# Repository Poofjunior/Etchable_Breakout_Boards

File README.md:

# A Collection of Etchable Breakout Boards

## Basic Info  
To open these breakout boards, you'll need the 
[HMCEagleLibrary](https://github.com/Poofjunior/HMCEagleLibrary)

Be careful when etching!

## References

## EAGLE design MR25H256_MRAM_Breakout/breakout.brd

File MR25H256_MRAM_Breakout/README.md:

# MR25H256 Etchable Breakout Board

## Basic Info  
The MR25H256 is a 262 kilobit magnetoresistive random-access memory chip 
that communicates over SPI interface. 

Be careful when etching!

## References
1. [The Datasheet](http://media.digikey.com/pdf/Data%20Sheets/EverSpin%20Technologies/MR25H256_Datasheet_Rev8.pdf)

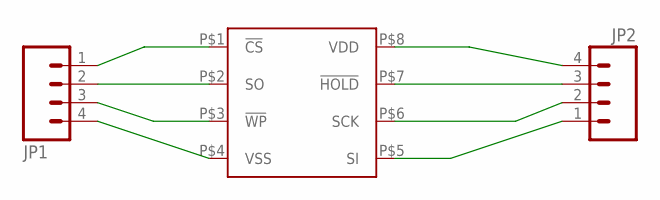
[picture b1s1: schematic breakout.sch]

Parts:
JP1, JP2: M04PTH; 1X04
U$1: MR25H256; DFN8

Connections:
unnamed: JP1.1, U$1.P$1 (!CS)
unnamed: JP1.2, U$1.P$2 (SO)
unnamed: JP1.3, U$1.P$3 (!WP)
unnamed: JP1.4, U$1.P$4 (VSS)
unnamed: JP2.1, U$1.P$5 (SI)
unnamed: JP2.2, U$1.P$6 (SCK)
unnamed: JP2.3, U$1.P$7 (!HOLD)
unnamed: JP2.4, U$1.P$8 (VDD)

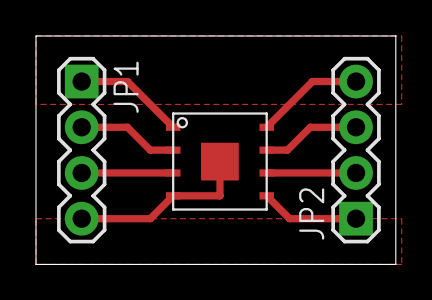
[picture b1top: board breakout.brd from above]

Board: 2 copper layers, 20.0 x 12.7 mm, 3 parts (0 on the bottom side), 8 nets.

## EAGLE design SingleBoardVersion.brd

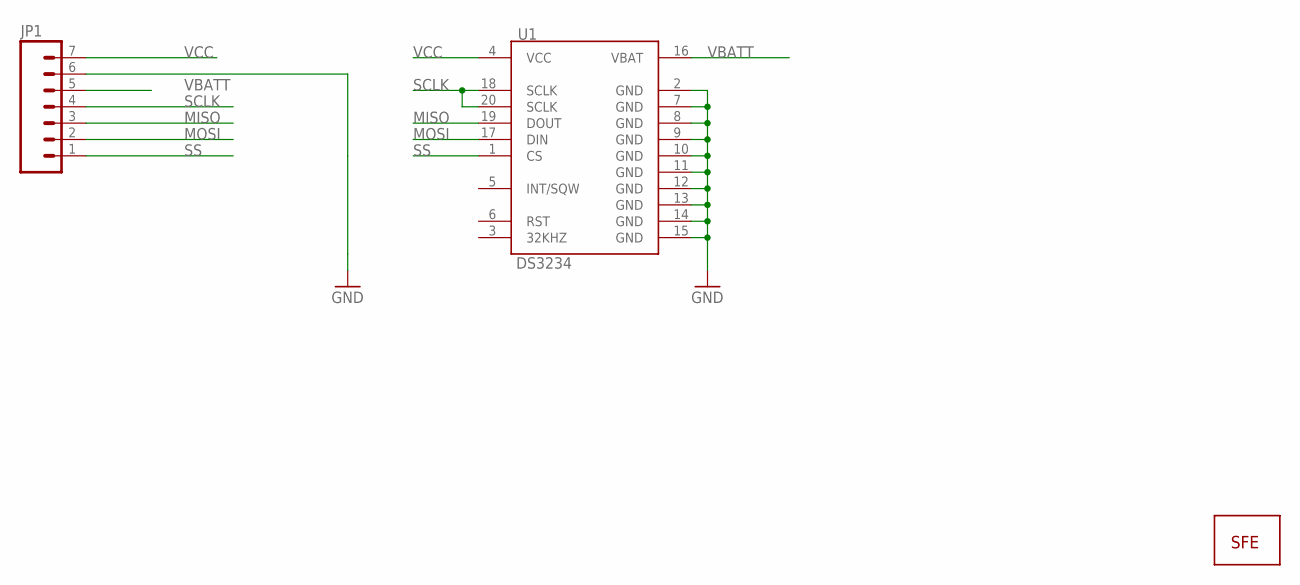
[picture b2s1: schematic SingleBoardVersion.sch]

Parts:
JP1: M07; 1X07
JP2: LOGO-SFESK; SFE-LOGO-FLAME
U1: DS3234

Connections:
GND: JP1.6, U1.2 (GND), U1.7 (GND), U1.8 (GND), U1.9 (GND), U1.10 (GND), U1.11 (GND), U1.12 (GND), U1.13 (GND), U1.14 (GND), U1.15 (GND)
MISO: JP1.3, U1.19 (DOUT)
MOSI: JP1.2, U1.17 (DIN)
SCLK: JP1.4, U1.18 (SCLK), U1.20 (SCLK)
SS: JP1.1, U1.1 (CS)
VBATT: JP1.5, U1.16 (VBAT)
VCC: JP1.7, U1.4 (VCC)

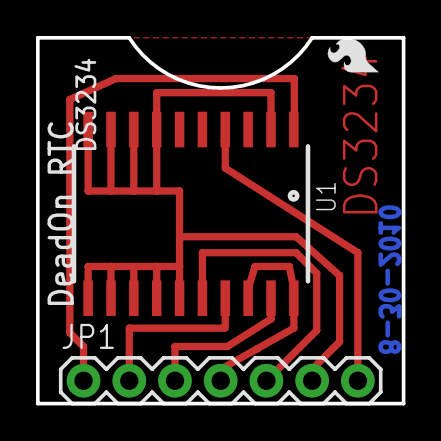
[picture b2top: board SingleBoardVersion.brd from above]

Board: 2 copper layers, 20.3 x 20.3 mm, 4 parts (0 on the bottom side), 7 nets.

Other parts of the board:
U2: CREATIVE_COMMONS

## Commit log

2013-02-22 added .gitignore
2013-02-24 updated README with references
2013-02-24 updated README with correct links
2013-02-24 added a picture
2013-02-24 fixed image size
2013-03-09 modifying file structure
2013-03-09 added mram breakout
2013-03-09 actually added mram breakout
2013-03-09 added a readme

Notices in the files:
parts and their libraries:
SparkFun-Connectors: Licensing: CC v3.0 Share-Alike You are welcome to use this library for commercial purposes.
SparkFun: Released under the Creative Commons Attribution Share-Alike 3.0 License
SparkFun: http://creativecommons.org/licenses/by-sa/3.0
